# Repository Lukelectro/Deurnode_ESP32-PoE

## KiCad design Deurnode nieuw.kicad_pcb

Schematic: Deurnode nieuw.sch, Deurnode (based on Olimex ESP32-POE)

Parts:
A1: Pololu_Breakout_A4988; Pololu_Breakout-16_15.2x20.3mm
C1: 2n2; C_Disc_D5.1mm_W3.2mm_P5.00mm
D1, D2: 1N4004; D_DO-41_SOD81_P10.16mm_Horizontal
D3: LED; LED_D3.0mm
J1: EXT1; PinSocket_1x10_P2.54mm_Vertical
J2: EXT2; PinSocket_1x10_P2.54mm_Vertical
J3: Conn_01x08; PinHeader_1x08_P2.54mm_Horizontal
J4, J9, J12: Screw_Terminal_01x03; TerminalBlock_RND_205-00288_1x03_P5.08mm_Horizontal
J5, J6: Conn_01x02; PinHeader_1x02_P2.54mm_Vertical
J7, J14, J15: Screw_Terminal_01x02; TerminalBlock_RND_205-00287_1x02_P5.08mm_Horizontal
J8: Screw_Terminal_01x04; TerminalBlock_RND_205-00289_1x04_P5.08mm_Horizontal
J18: BarrelJack_DC5.5F
J19: Jumper Use external 12V; PinHeader_1x02_P2.54mm_Vertical
J22: Force output ON; PinHeader_1x02_P2.54mm_Vertical
K1: SONGLE SRD-05VDC-SL-C; Relay_SPDT_SANYOU_SRD_Series_Form_C
OK1, OK2: PC814; DIL04
R1: 10R; R_Axial_DIN0207_L6.3mm_D2.5mm_P7.62mm_Horizontal
R2: 4k7; R_Axial_DIN0207_L6.3mm_D2.5mm_P7.62mm_Horizontal
R3: 330R; R_Axial_DIN0207_L6.3mm_D2.5mm_P7.62mm_Horizontal
R5: 47k; R_Axial_DIN0207_L6.3mm_D2.5mm_P7.62mm_Horizontal
R6, R7, R8, R9: 220k; R_Axial_DIN0207_L6.3mm_D2.5mm_P7.62mm_Horizontal
R10: 2k2; R_Axial_DIN0207_L6.3mm_D2.5mm_P7.62mm_Horizontal
U1: IRFZ44N; TO-220
U2: OKI-78SR-5_1.5-W36-C; Converter_DCDC_muRata_OKI-78SR_Vertical

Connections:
3V3: A1.2, A1.10, A1.13, A1.14, J1.2, J3.8
+5V: D1.1 (K), J1.1, J4.2, J5.2, J19.2, K1.5, R2.2
+12V: A1.8, D2.1 (K), J4.1, J7.1, J9.1, J18.1, U2.1 (IN)
GND: A1.1, A1.7, C1.2, D3.1, J1.3, J3.6, J4.3, J6.2, J7.2, J9.3, J18.2, J18.3, J22.2, OK1.3, OK2.3, R5.2, U1.3, U2.2 (GND)
GPI35: J2.3, J3.4
GPI36_U1RXD: C1.1, J2.2, OK1.4, R3.2
GPI39: J2.1, OK2.4
GPIO2_HS2_DATA0: A1.16, J1.7
GPIO4_U1TXD: A1.9, J1.9
GPIO5_SPI_C5: A1.15, J1.10
GPIO13_I2C-SDA: J2.10, J3.3
GPIO14_HS2_CLK: J2.9, J3.2
GPIO15_HS2_CMD: J2.8, J3.1
GPIO16_I2C-SCL: J2.7, R1.2
GPIO32: J2.6, J3.7
GPIO33: J2.5, J3.5
unnamed: A1.3, J8.1
unnamed: A1.4, J8.2
unnamed: A1.5, J8.3
unnamed: A1.6, J8.4
unnamed: D1.2 (A), D2.2 (A), J5.1, J9.2, J22.1, K1.2, R2.1, R10.1, U1.2
unnamed: D3.2, R10.2
unnamed: J6.1, R3.1
unnamed: J12.1, K1.4
unnamed: J12.2, K1.1
unnamed: J12.3, K1.3
unnamed: J14.1, R6.1
unnamed: J14.2, R7.1
unnamed: J15.1, R8.1
unnamed: J15.2, R9.1
unnamed: J19.1, U2.3 (OUT)
unnamed: OK1.1, R6.2
unnamed: OK1.2, R7.2
unnamed: OK2.1, R8.2
unnamed: OK2.2, R9.2
unnamed: R1.1, R5.1, U1.1

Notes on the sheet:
ESP32-PoE connectors
Power
Rfid
Buzzer output 5V
Schakelaar
Stappen motor
Opto Coupler input 1
Relais output
Opto Coupler input 2
12V
FET output
Coil +
Coil -
Ext. gnd
+12V
GND
Common
Default 230V AC
(12V buzzer, relay, door solenoid, anything)

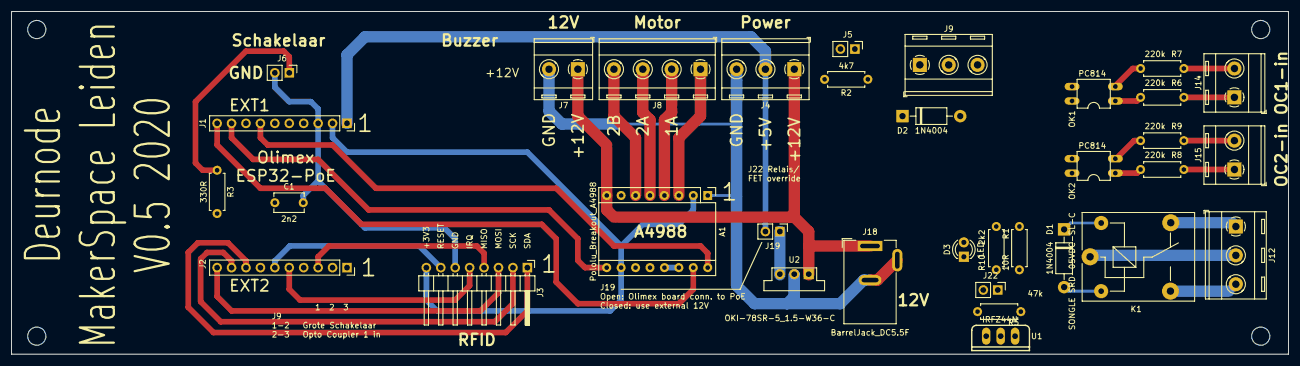
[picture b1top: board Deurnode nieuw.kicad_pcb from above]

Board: 2 copper layers, 224.8 x 60.3 mm, 34 parts (0 on the bottom side), 36 nets.

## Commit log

2020-03-06 Simplified by using FET to drive relay OR buzzer, removed GND on 230VAC side of opto. TODO: ERC check / stepper driver rst,sleep,ms pins. Note: My kicad version is different so symbols might have cha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
2020-03-06 started on re-routing PCB increasing clearance from mains and using netclasses
2020-03-06 add groundplane
